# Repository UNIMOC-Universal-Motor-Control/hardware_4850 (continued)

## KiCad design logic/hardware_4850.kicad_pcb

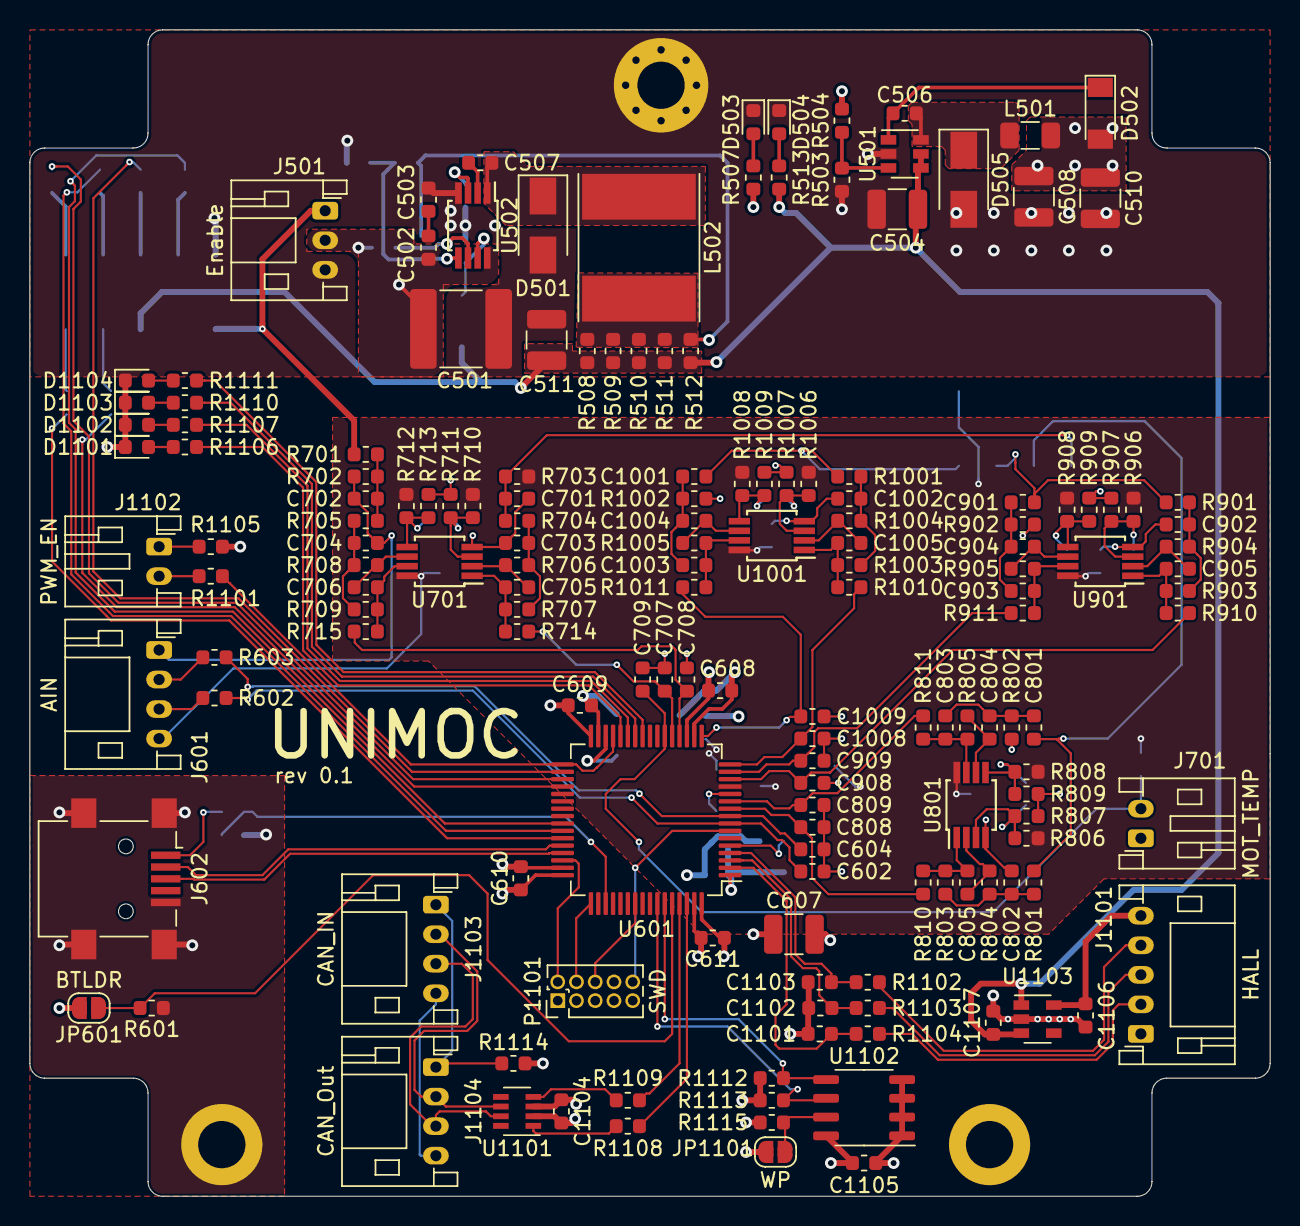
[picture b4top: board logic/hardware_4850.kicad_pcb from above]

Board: 4 copper layers, 84.0 x 79.0 mm, 202 parts (0 on the bottom side), 122 nets.

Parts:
C501: 10u; C_2220_5650Metric
C502, C503, C506, C507, C601, C602, C604, C605, C608, C609, C610, C611, C612, C701, C707, C708, C709, C710, C711, C712, C806, C807, C808, C810, C906, C907, C908, C910, C1006, C1007, C1008, C1010, C1101, C1102, C1103, C1104, C1105: 100n; C_0603_1608Metric
C504, C508, C510, C511, C512: 22u; C_1210_3225Metric
C505, C1106, C1107: 1u; C_0603_1608Metric
C509: 2n2; C_0603_1608Metric
C603, C606, C607: 10u; C_1210_3225Metric
C702, C705, C706: 1n; C_0603_1608Metric
C703, C704: 10n; C_0603_1608Metric
C801, C802, C804, C901, C902, C904, C1001, C1002, C1004: 4n7; C_0603_1608Metric
C803, C805, C903, C905, C1003, C1005: 47p; C_0603_1608Metric
C809, C909, C1009: 100p; C_0603_1608Metric
D501, D505: SS110R3G; D_SMA
D502, D506: PMLL4153; D_MiniMELF
D503: 3V3; LED_0603_1608Metric
D504: 12V; LED_0603_1608Metric
D1101: RUN; LED_0603_1608Metric
D1102: ERROR; LED_0603_1608Metric
D1103: FW; LED_0603_1608Metric
D1104: PWM; LED_0603_1608Metric
FB501, FB502: Ferrite_Bead_Small; R_0603_1608Metric
H101: GND; MountingHole_3.2mm_M3_Pad_Via
H102, H103: GND; MountingHole_3.2mm_M3_ISO14580_Pad
J101: PWM; PinHeader_2x05_P2.54mm_Vertical_SMD
J102: ADC; PinHeader_2x05_P2.54mm_Vertical_SMD
J501: Enable; JST_PH_S3B-PH-K_1x03_P2.00mm_Horizontal
J601: AIN; JST_PH_S4B-PH-K_1x04_P2.00mm_Horizontal
J602: USB_B_Mini; USB_Mini-B_Lumberg_2486_01_Horizontal
J701: MOT_TEMP; JST_PH_S2B-PH-K_1x02_P2.00mm_Horizontal
J1101: HALL; JST_PH_S5B-PH-K_1x05_P2.00mm_Horizontal
J1102: PWM_EN; JST_PH_S2B-PH-K_1x02_P2.00mm_Horizontal
J1103: CAN_IN; JST_PH_S4B-PH-K_1x04_P2.00mm_Horizontal
J1104: CAN_Out; JST_PH_S4B-PH-K_1x04_P2.00mm_Horizontal
JP601: BTLDR; SolderJumper-2_P1.3mm_Open_RoundedPad1.0x1.5mm
JP1101: WP; SolderJumper-2_P1.3mm_Open_RoundedPad1.0x1.5mm
L501: 4u7; L_1206_3216Metric
L502: 330u; L_Taiyo-Yuden_NR-80xx_HandSoldering
P1101: SWD; PinHeader_2x05_P1.27mm_Vertical
R501: 220k; R_0603_1608Metric
R502: 100k; R_0603_1608Metric
R503, R505, R601, R602, R603, R605, R710, R711, R712, R713, R806, R807, R808, R809, R906, R907, R908, R909, R1006, R1007, R1008, R1009, R1115: 11k; R_0603_1608Metric
R504: 34k; R_0603_1608Metric
R506: 2k7; R_0603_1608Metric
R507, R1101, R1102, R1103, R1104, R1105, R1106, R1107, R1110, R1111: 510R; R_0603_1608Metric
R508, R509, R510, R511, R512, R1108, R1109, R1114: 11R; R_0603_1608Metric
R513: 3k3; R_0603_1608Metric
R604, R704, R705, R707, R709, R802, R902, R1002, R1112, R1113: 4k7; R_0603_1608Metric
R606, R607, R608, R609, R610, R611: 1R1; R_0603_1608Metric
R701: 24k 0.1%; R_0603_1608Metric
R702: 1k2 0.1%; R_0603_1608Metric
R703, R716: 10k 0.1%; R_0603_1608Metric
R706, R708: 47k; R_0603_1608Metric
R714, R715, R810, R811, R910, R911, R1010, R1011: 21R; R_0603_1608Metric
R801, R803, R901, R903, R1001, R1003: 9k1; R_0603_1608Metric
R804, R904, R1004: 470k; R_0603_1608Metric
R805, R905, R1005: 910k; R_0603_1608Metric
U501: LMR12010Y; SOT-23-6
U502: LM5008; MSOP-8_3x3mm_P0.65mm
U601: STM32F730R8Tx; LQFP-64_10x10mm_P0.5mm
U701, U801, U901, U1001: GS8632-MR; MSOP-8_3x3mm_P0.65mm
U1101: TCAN334; SOT-23-8
U1102: 24LC04; SO-8_3.9x4.9mm_P1.27mm
U1103: AP2204K-5.0; SOT-23-5
X601: SM44T; Oscillator_SMD_Abracon_ASE-4Pin_3.2x2.5mm

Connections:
+1V2: C603.1, U601.30
+3.3VADC: C512.1, C605.1, C606.1, C710.1, C810.1, C910.1, C1010.1, FB501.1, J102.1, J601.4, R703.2, R710.2, R712.2, R716.2, R806.1, R808.1, R906.1, R908.1, R1006.1, R1008.1, U601.13, U701.8, U801.8, U901.8, U1001.8
+3V3: C508.1, C510.1, C601.1, C607.1, C608.1, C609.1, C610.1, C611.1, C612.1, C1104.1, C1105.1, D502.2, FB501.2, JP601.2, JP1101.1, L501.2, P1101.1, R504.2, R507.2, R1105.2, R1112.1, R1113.1, U601.1, U601.19, U601.32, U601.48, U601.64, U1101.3, U1102.8, X601.1, X601.4
+12V: C504.1, C511.1, C1107.1, D506.2, J101.5, R508.1, R509.1, R510.1, R511.1, R512.1, R513.1, U501.4, U501.5, U1103.1, U1103.3
+48V: J101.1, J501.1, R701.2
/controller/AIN_ACC: C602.1, R602.2, U601.8
/controller/AIN_CUR_A: C808.2, R810.1, U601.10
/controller/AIN_CUR_A_AC: C809.2, R811.1, U601.11
/controller/AIN_DCC: C604.1, R603.2, U601.9
/controller/BTLDR: JP601.1, R601.2, U601.60
/controller/CAN_RX: R1109.2, U601.61
/controller/CAN_TX: R1108.2, U601.62
/controller/CLK: U601.5, X601.3
/controller/EEPROM_SCL: R1113.2, U601.58, U1102.6
/controller/EEPROM_SDA: R1112.2, U601.59, U1102.5
/controller/Ia: C801.2, J102.6, R801.2
/controller/Ib: C901.2, J102.4, R901.2
/controller/Ic: C1001.2, J102.2, R1001.2
/controller/PwmAH: J101.4, R609.1
/controller/PwmAL: J101.6, R606.1
/controller/PwmBH: J101.8, R610.1
/controller/PwmBL: J101.10, R607.1
/controller/PwmCH: J101.9, R611.1
/controller/PwmCL: J101.7, R608.1
/controller/TCK-SWCLK: P1101.4, U601.49
/controller/TDO-SWO: P1101.6, U601.55
/controller/TMS-SWDIO: P1101.2, U601.46
/controller/Temp+: C701.1, J102.8, R703.1, R704.2
/controller/USB_DM: J602.2, U601.44
/controller/USB_DP: J602.3, U601.45
/controller/USB_VBUS: R604.2, R605.2, U601.51
/controller/\RESET: P1101.10, U601.7
/controller/analog/BrdgTemp: C707.1, R714.2, U601.21
/controller/analog/IbAC: C909.2, R911.1, U601.15
/controller/analog/IbDC: C908.2, R910.1, U601.14
/controller/analog/IcAC: C1009.2, R1011.1, U601.17
/controller/analog/IcDC: C1008.2, R1010.1, U601.16
/controller/analog/MotTemp: C709.1, J701.2, R716.1, U601.22
/controller/analog/Vdc: C708.1, R715.2, U601.20
/controller/interfaces/HallA: C1101.1, R1104.1, U601.2
/controller/interfaces/HallB: C1102.1, R1103.1, U601.3
/controller/interfaces/HallC: C1103.1, R1102.1, U601.4
/controller/interfaces/LED_ERROR: R1107.2, U601.27
/controller/interfaces/LED_MODE: R1110.2, U601.26
/controller/interfaces/LED_PWM: R1111.2, U601.25
/controller/interfaces/LED_RUN: R1106.2, U601.28
/controller/interfaces/PWM_EN: R1101.2, U601.29, U601.33
GNDA: C512.2, C602.2, C604.2, C605.2, C606.2, C701.2, C702.1, C703.1, C704.1, C707.2, C708.2, C709.2, C710.2, C711.2, C712.2, C802.1, C806.1, C807.1, C808.1, C809.1, C810.2, C902.1, C906.1, C907.1, C908.1, C909.1, C910.2, C1002.1, C1006.1, C1007.1, C1008.1, C1009.1, C1010.2, FB502.1, J102.3, J102.5, J102.7, J102.9, J102.10, J601.1, J701.1, R702.2, R711.1, R713.1, R802.2, R807.2, R809.2, R902.2, R907.2, R909.2, R1002.2, R1007.2, R1009.2, U601.12, U701.4, U801.4, U901.4, U1001.4
GNDD: C501.2, C503.2, C504.2, C505.1, C508.2, C510.2, C511.2, C601.2, C603.2, C607.2, C608.2, C609.2, C610.2, C611.2, C612.2, C1101.2, C1102.2, C1103.2, C1104.2, C1105.2, C1106.2, C1107.2, D501.2, D503.1, D504.1, D505.2, D1101.1, D1102.1, D1103.1, D1104.1, FB502.2, H101.1, H102.1, H103.1, J101.2, J501.3, J602.5, J602.6, J1101.1, P1101.3, P1101.5, R502.1, R503.1, R506.1, R601.1, R605.1, R1114.2, R1115.2, U501.2, U502.4, U601.18, U601.31, U601.47, U601.63, U1101.2, U1102.1, U1102.2, U1102.3, U1102.4, U1103.2, X601.2
unnamed: C501.1, C502.1, J501.2, R501.2, U502.8
unnamed: C502.2, C503.1
unnamed: C505.2, D506.1, U502.7
unnamed: C506.1, D505.1, L501.1, U501.6
unnamed: C506.2, D502.1, U501.1
unnamed: C507.1, D501.1, L502.1, U502.1
unnamed: C507.2, U502.2
unnamed: C509.1, L502.2, R505.2, R508.2, R509.2, R510.2, R511.2, R512.2
unnamed: C509.2, R505.1, R506.2, U502.5
unnamed: C702.2, R701.1, R702.1, R705.2
unnamed: C703.2, R704.1, R706.2, R707.2
unnamed: C704.2, R705.1, R708.2, R709.2
unnamed: C705.1, R707.1, R714.1, U701.1
unnamed: C705.2, R706.1, U701.2
unnamed: C706.1, R709.1, R715.1, U701.7
unnamed: C706.2, R708.1, U701.6
unnamed: C711.1, R710.1, R711.2, U701.3
unnamed: C712.1, R712.1, R713.2, U701.5
unnamed: C801.1, C803.2, C804.2, R802.1
unnamed: C802.2, R801.1, R803.2, R804.2
unnamed: C803.1, R805.1, R811.2, U801.7
unnamed: C804.1, R805.2, U801.6
unnamed: C805.1, R804.1, U801.2
unnamed: C805.2, R803.1, R810.2, U801.1
unnamed: C806.2, R806.2, R807.1, U801.3
unnamed: C807.2, R808.2, R809.1, U801.5
unnamed: C901.1, C903.2, C904.2, R902.1
unnamed: C902.2, R901.1, R903.2, R904.2
unnamed: C903.1, R905.1, R911.2, U901.7
unnamed: C904.1, R905.2, U901.6
unnamed: C905.1, R904.1, U901.2
unnamed: C905.2, R903.1, R910.2, U901.1
unnamed: C906.2, R906.2, R907.1, U901.3
unnamed: C907.2, R908.2, R909.1, U901.5
unnamed: C1001.1, C1003.2, C1004.2, R1002.1
unnamed: C1002.2, R1001.1, R1003.2, R1004.2
unnamed: C1003.1, R1005.1, R1011.2, U1001.7
unnamed: C1004.1, R1005.2, U1001.6
unnamed: C1005.1, R1004.1, U1001.2
unnamed: C1005.2, R1003.1, R1010.2, U1001.1
unnamed: C1006.2, R1006.2, R1007.1, U1001.3
unnamed: C1007.2, R1008.2, R1009.1, U1001.5
unnamed: C1106.1, J1101.5, U1103.5
unnamed: D503.2, R507.1
unnamed: D504.2, R513.2
unnamed: D1101.2, R1106.1
unnamed: D1102.2, R1107.1
unnamed: D1103.2, R1110.1
unnamed: D1104.2, R1111.1
unnamed: J601.2, R603.1
unnamed: J601.3, R602.1
unnamed: J602.1, R604.1
unnamed: J1101.2, R1104.2
unnamed: J1101.3, R1103.2
unnamed: J1101.4, R1102.2
unnamed: J1102.1, R1105.1
unnamed: J1102.2, R1101.1
unnamed: J1103.1, J1104.1, R1114.1
unnamed: J1103.2, J1104.2, U1101.6
unnamed: J1103.3, J1104.3, U1101.7
unnamed: J1103.4, J1104.4
unnamed: JP1101.2, R1115.1, U1102.7
unnamed: R501.1, U502.6
unnamed: R502.2, U502.3
unnamed: R503.2, R504.1, U501.3
unnamed: R606.2, U601.34
unnamed: R607.2, U601.35
unnamed: R608.2, U601.36
unnamed: R609.2, U601.41
unnamed: R610.2, U601.42
unnamed: R611.2, U601.43
unnamed: R1108.1, U1101.1
unnamed: R1109.1, U1101.4

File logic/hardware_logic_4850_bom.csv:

Reference, Quantity, Value, Footprint, Datasheet, Part#
C501 ,1,"10u","Capacitor_SMD:C_2220_5650Metric","~","FS55X106K101EHG"
C505 C1107 C1106 ,3,"1u","Capacitor_SMD:C_0603_1608Metric","~","CL10B105KANC"
C506 C502 C503 C507 C610 C609 C608 C601 C611 C612 C605 C602 C604 C710 C701 C708 C707 C709 C711 C712 C810 C808 C807 C806 C910 C908 C907 C906 C1010 C1008 C1007 C1006 C1105 C1101 C1102 C1103 C1104 ,37,"100n","Capacitor_SMD:C_0603_1608Metric","","CL10B104KBNC"
C508 C510 C504 C512 C511 ,5,"22u","Capacitor_SMD:C_1210_3225Metric","","CL32B226MOJNNNE"
C509 ,1,"2n2","Capacitor_SMD:C_0603_1608Metric","","GRM1885C1H222JA01D"
C607 C606 C603 ,3,"10u","Capacitor_SMD:C_1210_3225Metric","~","CL32B106KLJNNNE"
C702 C704 C703 C804 C802 C801 C904 C902 C901 C1004 C1002 C1001 ,12,"1n","Capacitor_SMD:C_0603_1608Metric","~","VJ0603Y102JXACW1BC"
C706 C705 C803 C805 C903 C905 C1003 C1005 ,8,"100p","Capacitor_SMD:C_0603_1608Metric","~","0603B101K500CT"
C809 C909 C1009 ,3,"10n","Capacitor_SMD:C_0603_1608Metric","~"
D1101 ,1,"RUN","LED_SMD:LED_0603_1608Metric","","598-8070-107F"
D1102 ,1,"ERROR","LED_SMD:LED_0603_1608Metric","","598-8070-107F"
D1103 ,1,"FW","LED_SMD:LED_0603_1608Metric","","598-8070-107F"
D1104 ,1,"PWM","LED_SMD:LED_0603_1608Metric","","598-8070-107F"
D501 D505 ,2,"SS110R3G","Diode_SMD:D_SMA","","SS110R3G"
D502 D506 ,2,"PMLL4153","Diode_SMD:D_MiniMELF","~","PMLL4153,115"
D503 ,1,"3V3","LED_SMD:LED_0603_1608Metric","","598-8070-107F"
D504 ,1,"12V","LED_SMD:LED_0603_1608Metric","","598-8070-107F"
FB501 FB502 ,2,"Ferrite_Bead_Small","Resistor_SMD:R_0603_1608Metric","~","ACML-0603-2000"
H101 ,1,"GND","MountingHole:MountingHole_3.2mm_M3_Pad_Via","~"
H102 H103 ,2,"GND","MountingHole:MountingHole_3.2mm_M3_ISO14580_Pad","~"
J101 ,1,"PWM","Connector_PinHeader_2.54mm:PinHeader_2x05_P2.54mm_Vertical_SMD","~","C124391"
J102 ,1,"ADC","Connector_PinHeader_2.54mm:PinHeader_2x05_P2.54mm_Vertical_SMD","~","C124391"
J1101 ,1,"HALL","Connector_JST:JST_PH_S5B-PH-K_1x05_P2.00mm_Horizontal","~","C157923"
J1102 ,1,"PWM_EN","Connector_JST:JST_PH_S2B-PH-K_1x02_P2.00mm_Horizontal","~","C157929"
J1103 ,1,"CAN_IN","Connector_JST:JST_PH_S4B-PH-K_1x04_P2.00mm_Horizontal","~","C157926"
J1104 ,1,"CAN_Out","Connector_JST:JST_PH_S4B-PH-K_1x04_P2.00mm_Horizontal","~","C157926"
J501 ,1,"Enable","Connector_JST:JST_PH_S3B-PH-K_1x03_P2.00mm_Horizontal","~","C157929"
J601 ,1,"AIN","Connector_JST:JST_PH_S4B-PH-K_1x04_P2.00mm_Horizontal","~","C157926"
J602 ,1,"USB_B_Mini","Connector_USB:USB_Mini-B_Lumberg_2486_01_Horizontal","~","C69074"
J701 ,1,"MOT_TEMP","Connector_JST:JST_PH_S2B-PH-K_1x02_P2.00mm_Horizontal","~","C157929"
JP1101 ,1,"WP","Jumper:SolderJumper-2_P1.3mm_Open_RoundedPad1.0x1.5mm","~"
JP601 ,1,"BTLDR","Jumper:SolderJumper-2_P1.3mm_Open_RoundedPad1.0x1.5mm","~"
L501 ,1,"4u7","Inductor_SMD:L_1206_3216Metric","","MIP25204R7MBE"
L502 ,1,"330u","Inductor_SMD:L_Taiyo-Yuden_NR-80xx_HandSoldering","","SMNR8040-331MT"
P1101 ,1,"SWD","Connector_PinHeader_1.27mm:PinHeader_2x05_P1.27mm_Vertical",""
R501 ,1,"220k","Resistor_SMD:R_0603_1608Metric","","CR0603JA0224G"
R502 ,1,"100k","Resistor_SMD:R_0603_1608Metric","","CR0603-JW-104ELF"
R503 R505 R601 R605 R602 R603 R708 R712 R713 R706 R710 R711 R808 R809 R806 R807 R804 R908 R909 R906 R907 R904 R1008 R1009 R1006 R1007 R1004 R1112 R1113 R1115 R1101 R1105 ,32,"11k","Resistor_SMD:R_0603_1608Metric","","MCR03ERTJ113"
R504 ,1,"34k","Resistor_SMD:R_0603_1608Metric","","ERJ-PA3F3402V"
R506 ,1,"2k7","Resistor_SMD:R_0603_1608Metric","","RS-03K272JT"
R507 R1104 R1103 R1102 R1106 R1107 R1110 R1111 ,8,"510R","Resistor_SMD:R_0603_1608Metric","","MCR03ERTJ511"
R512 R511 R510 R509 R508 R1114 R1108 R1109 ,8,"11R","Resistor_SMD:R_0603_1608Metric","","MCR03ERTJ11R"
R513 ,1,"910R","Resistor_SMD:R_0603_1608Metric","","MCR03ERTJ911"
R604 R705 R709 R704 R707 R803 R801 R903 R901 R1003 R1001 ,11,"4k7","Resistor_SMD:R_0603_1608Metric","~","0603WAJ0472T5E"
R609 R610 R611 R606 R607 R608 ,6,"1R1","Resistor_SMD:R_0603_1608Metric","~","MCR03ERTJ1R1"
R702 ,1,"560R 0.1%","Resistor_SMD:R_0603_1608Metric","~","AR03BTDX5600"
R703 R701 R716 ,3,"10k 0.1%","Resistor_SMD:R_0603_1608Metric","~","ARG03BTC1002"
R715 R714 R811 R810 R911 R910 R1011 R1010 ,8,"21R","Resistor_SMD:R_0603_1608Metric","~"
R802 R902 R1002 ,3,"47k","Resistor_SMD:R_0603_1608Metric","~"
R805 R905 R1005 ,3,"1M","Resistor_SMD:R_0603_1608Metric","~"
U1101 ,1,"TCAN334","Package_TO_SOT_SMD:SOT-23-8","http://www.ti.com/lit/ds/symlink/tcan337.pdf","TCAN334DCNR"
U1102 ,1,"24LC04","Package_SO:SO-8_3.9x4.9mm_P1.27mm","http://ww1.microchip.com/downloads/en/DeviceDoc/21708K.pdf","AT34C04-SS5M-B"
U1103 ,1,"AP2204K-5.0","Package_TO_SOT_SMD:SOT-23-5","https://www.diodes.com/assets/Datasheets/AP2204.pdf"
U501 ,1,"LMR12010Y","Package_TO_SOT_SMD:SOT-23-6","http://www.ti.com/lit/ds/symlink/lmr12010.pdf","LMR12010YMK/NOPB"
U502 ,1,"LM5008","Package_SO:MSOP-8_3x3mm_P0.65mm","","LM5008MMX/NOPB"
U601 ,1,"STM32F730R8Tx","Package_QFP:LQFP-64_10x10mm_P0.5mm","http://www.st.com/st-web-ui/static/active/en/resource/techni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","511-STM32F730R8T6"
U701 U801 U901 U1001 ,4,"GS8632-MR","Package_SO:MSOP-8_3x3mm_P0.65mm","","GS8632-MR"
X601 ,1,"SM44T","Oscillator:Oscillator_SMD_Abracon_ASE-4Pin_3.2x2.5mm","${KIPRJMOD}/datasheets/sm44t203.3v.pdf","SM4444TEV-20.0M"

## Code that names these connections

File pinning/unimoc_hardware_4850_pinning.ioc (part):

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Mcu.Name=STM32F730R8Tx
Mcu.Package=LQFP64
Mcu.UserName=STM32F730R8Tx
PA0-WKUP.GPIOParameters=GPIO_Label
PA0-WKUP.GPIO_Label=AIN_CUR_B
PA0-WKUP.Signal=ADCx_IN0
PA1.GPIOParameters=GPIO_Label
PA1.GPIO_Label=AIN_CUR_B_AC
PA1.Signal=ADCx_IN1
PA10.Signal=S_TIM1_CH3
PA11.Mode=Device_Only
PA11.Signal=USB_OTG_FS_DM
PA12.Mode=Device_Only
PA12.Signal=USB_OTG_FS_DP
PA13.Mode=JTAG_5_pins
PA13.Signal=SYS_JTMS-SWDIO
PA14.Mode=JTAG_5_pins
PA14.Signal=SYS_JTCK-SWCLK
PA15.Mode=JTAG_5_pins
PA15.Signal=SYS_JTDI
PA2.GPIOParameters=GPIO_Label
PA2.GPIO_Label=AIN_CUR_A
PA2.Signal=ADCx_IN2
PA3.GPIOParameters=GPIO_Label
PA3.GPIO_Label=AIN_CUR_A_AC
PA3.Signal=ADCx_IN3
PA4.GPIOParameters=GPIO_Label
PA4.GPIO_Label=AIN_VDC
PA4.Signal=ADCx_IN4
PA5.GPIOParameters=GPIO_Label
PA5.GPIO_Label=AIN_BRDG_TEMP
PA5.Signal=ADCx_IN5
PA6.GPIOParameters=GPIO_Label
PA6.GPIO_Label=AIN_MOT_TEMP
PA6.Signal=ADCx_IN6
PA8.Signal=S_TIM1_CH1
PA9.Signal=S_TIM1_CH2
PB0.GPIOParameters=GPIO_Label
PB0.GPIO_Label=LED_PWM
PB0.Signal=GPIO_Output
PB1.GPIOParameters=GPIO_Label
PB1.GPIO_Label=LED_MODE
PB1.Signal=GPIO_Output
PB10.GPIOParameters=GPIO_Label
PB10.GPIO_Label=LED_RUN
PB10.Signal=GPIO_Output
PB11.GPIOParameters=GPIO_Label
PB11.GPIO_Label=ENABLE_PWM
PB11.Signal=GPIO_Output
PB12.Mode=Activate-Break-Input
PB12.Signal=TIM1_BKIN
PB13.Mode=Output Compare1 CH1 CH1N
PB13.Signal=TIM1_CH1N
PB14.Mode=Output Compare2 CH2 CH2N
PB14.Signal=TIM1_CH2N
PB15.Mode=Output Compare3 CH3 CH3N
PB15.Signal=TIM1_CH3N
PB2.GPIOParameters=GPIO_Label
PB2.GPIO_Label=LED_ERROR
PB2.Signal=GPIO_Output
PB3.Mode=JTAG_5_pins
PB3.Signal=SYS_JTDO-SWO
PB4.Mode=JTAG_5_pins
PB4.Signal=SYS_JTRST
PB6.Mode=I2C
PB6.Signal=I2C1_SCL
PB7.Mode=I2C
PB7.Signal=I2C1_SDA
PB8.Mode=Master
PB8.Signal=CAN1_RX
PB9.Mode=Master
PB9.Signal=CAN1_TX
PC0.GPIOParameters=GPIO_Label
PC0.GPIO_Label=AIN_ACC
PC0.Signal=ADCx_IN10
PC1.GPIOParameters=GPIO_Label
PC1.GPIO_Label=AIN_DCC
PC1.Signal=ADCx_IN11
PC10.GPIOParameters=GPIO_Label
PC10.GPIO_Label=USB_VBUS
PC10.Signal=GPIO_Input
PC13.GPIOParameters=GPIO_Label
PC13.GPIO_Label=HALL_A
PC13.Signal=GPIO_Input
PC14-OSC32_IN.GPIOParameters=GPIO_Label
PC14-OSC32_IN.GPIO_Label=HALL_B
PC14-OSC32_IN.Signal=GPIO_Input
PC15-OSC32_OUT.GPIOParameters=GPIO_Label
PC15-OSC32_OUT.GPIO_Label=HALL_C
PC15-OSC32_OUT.Signal=GPIO_Input
PC2.GPIOParameters=GPIO_Label
PC2.GPIO_Label=AIN_CUR_C
PC2.Signal=ADCx_IN12
PC3.GPIOParameters=GPIO_Label
PC3.GPIO_Label=AIN_CUR_C_AC
PC3.Signal=ADCx_IN13
PH0-OSC_IN.Mode=HSE-External-Clock-Source
PH0-OSC_IN.Signal=RCC_OSC_IN
PH1-OSC_OUT.Mode=HSE-External-Clock-Source
PH1-OSC_OUT.Signal=RCC_OSC_OUT
RCC.HSE_VALUE=25000000
board=custom

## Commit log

2019-10-25 added simulation for current filters
2019-10-25 added kicad project
    added schematics for other projects as basis.
2019-10-25 removed useless parts
2019-10-25 updated components
    - changed shunt to 1mR variant
    - changed Fet Driver to TI type
    - changed DC Link caps.
2019-10-26 added mcu pinning
2019-10-26 finished Rev0 of schematics
2019-10-28 added enclosure
    - first placing of power stage finished
2019-10-29 started placing of logic board
2019-11-01 more logic placing, switched halls for better routing
2019-11-02 finished placing :)
2019-11-07 changed shunts to standard footprint for more alternatives
2019-11-08 started routing of power stage
2019-11-09 finished power stage routing
2019-11-09 routing of logic supply finished
2019-11-09 started routing of logic board
2019-11-10 added monting holes for coolplate
2019-11-12 routed someof the analog systems
2019-11-16 changed design rules or logic board to smaller wires
2019-11-16 routing..
2019-11-16 finished routing of logic pcb
2019-11-17 made 3d design for mounting in enclosure
2019-11-18 made logic board leave bolt area
2019-11-18 added VCC Diode to LM5008
2019-11-19 Made gerbers ready to order
2019-11-20 seperated the boards in 2 projects
2020-01-19 re thought highpass because of to low input impedance
2020-01-21 updated current filters for low current hp
2020-01-25 found the first error SDA and SCL swaped
2020-02-17 added new filter designs
2020-02-17 highpass with 40db gain OP is to slow
2020-02-18 added boms
2020-02-19 created bom with prices
2020-02-26 added voltage filter to the sim
2020-02-26 changed values to new high precision values
2020-03-06 switched FET and Caps to real values
2020-03-21 second prototype dimensioning
2020-03-21 parts update
2020-04-21 new current filters
2020-04-24 fixed pwm_en bug
2020-05-03 droped ac filters
2020-10-09 coolplate design
2021-02-04 started new rev
2021-03-03 . just some filter stuff
2021-03-28 added new pinning for redesign and new simpler ac filter simulation
2021-03-28 redesign opamps and pinning
2021-03-29 fixed the pinning and started lcsc parts selection
2021-03-29 updated Phase schemati
2021-03-30 build top schematic
2021-03-30 added wheel speed sensor input
2021-03-31 finished schematics so far
2021-03-31 started the layout
2021-04-02 added screw terminals
2021-04-02 switched to old housing
2021-04-03 finished placing started layout
2021-04-04 26 routes to go
2021-04-25 adding vias
2021-04-28 added some more caps for decouppling
2021-05-17 started acs simulations
2021-05-17 clark pwm in sim
2021-05-18 added hfi pwm pattern to model
2021-05-18 :-1:
2021-05-20 added current amplifiers
2021-05-21 added all the filters
2021-05-21 added voltage filters
2021-05-22 added acs lt spice library
2021-05-24 split projects for stacked smaller boards
2021-05-25 added fully diff pre amp
2021-05-25 power board schematics finished.
2021-05-26 added supply connector for logic board
2022-12-04 updated to kicad 6
2022-12-04 start
